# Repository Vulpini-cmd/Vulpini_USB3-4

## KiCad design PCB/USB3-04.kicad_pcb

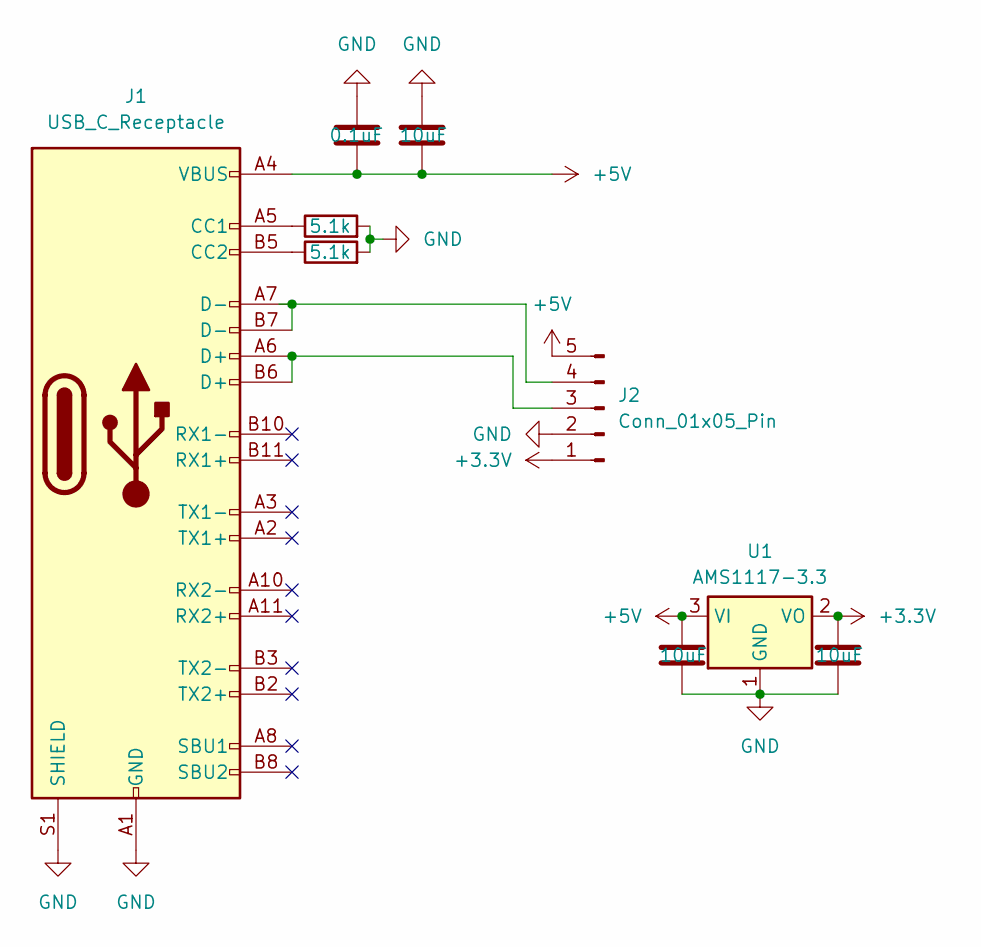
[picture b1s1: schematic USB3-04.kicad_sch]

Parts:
C1: 0.1uF; C_0805_2012Metric
C2, C3, C4: 10uF; C_0805_2012Metric
J1: USB_C_Receptacle; USB_C_Receptacle_Molex_105450-0101
J2: Conn_01x05_Pin; PinHeader_1x05_P2.54mm_Horizontal
R1, R2: 5.1k; C_0805_2012Metric
U1: AMS1117-3.3; SOT-223-3_TabPin2

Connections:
+3.3V: C4.1, J2.1, U1.2 (VO)
+5V: C1.2, C2.2, C3.1, J1.A4 (VBUS), J1.A9 (VBUS), J1.B4 (VBUS), J1.B9 (VBUS), J2.5, U1.3 (VI)
GND: C1.1, C2.1, C3.2, C4.2, J1.A1 (GND), J1.A12 (GND), J1.B1 (GND), J1.B12 (GND), J1.S1 (SHIELD), J2.2, R1.2, R2.2, U1.1 (GND)
unnamed: J1.A5 (CC1), R1.1
unnamed: J1.B5 (CC2), R2.1
unnamed: J1.A6 (D+), J1.B6 (D+), J2.3
unnamed: J1.A7 (D-), J1.B7 (D-), J2.4

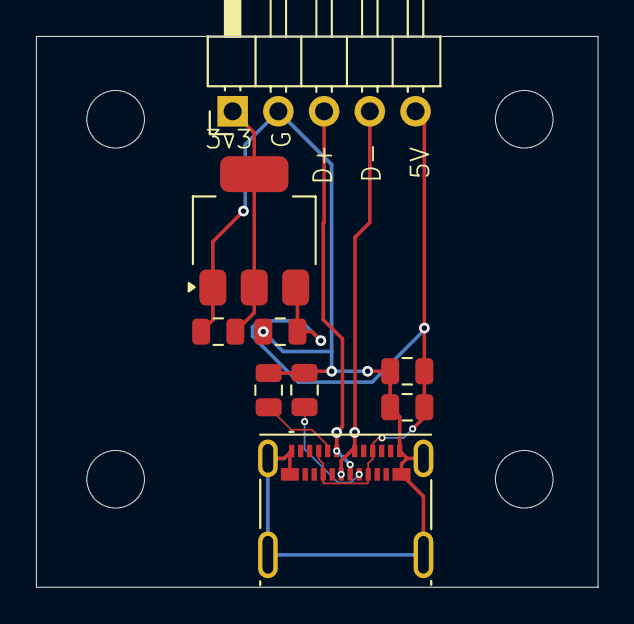
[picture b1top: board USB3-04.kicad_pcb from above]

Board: 2 copper layers, 31.2 x 30.6 mm, 9 parts (0 on the bottom side), 7 nets.
